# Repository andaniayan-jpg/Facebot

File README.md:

## Project Description

This is my small-scale AI smart assistant that I built completely from scratch using the ESP32-S3. I didn’t want to just make a simple breadboard project, so I designed a full custom PCB for it to make it look and feel like a proper product.

The device has a high-quality microphone with an amplifier so it can clearly pick up voice commands, and it also has a speaker so it can respond back properly. I added a TFT display to show smooth animations and expressions, so it doesn’t feel like a boring machine but more like a small gadget with some personality.

Everything is fitted inside a 3D-printed enclosure that I designed myself. I made sure the PCB, screen, mic, and speaker all fit properly and the finishing looks clean. This project combines hardware design, PCB making, wireless connectivity, and AI features into one compact device.

It’s basically my attempt at building a proper end-to-end AI gadget instead of just making a small demo.

## How to Use

1. Power the device using a USB cable.
2. Once it turns on, the TFT display will show an animation indicating that the assistant is ready.
3. Speak clearly near the microphone to give a voice command.
4. The assistant processes your request over Wi-Fi and responds back through the speaker.
5. The screen shows visual feedback while it is listening and responding.

Make sure the device is connected to Wi-Fi before using it for AI-based responses.

## Why I Made This Project

I made this project because I didn’t want to just keep learning things in theory. I wanted to actually build something real that combines electronics, coding, and AI in one proper device. Instead of copying some ready-made tutorial, I challenged myself to design everything — the PCB, the enclosure, and the full system integration.

I was also curious about how voice assistants actually work behind the scenes. We use them every day, but building one from scratch made me understand the hardware side, firmware side, and how wireless communication connects everything together.

This project was mainly about pushing myself to go beyond simple prototypes and create something that feels like an actual product.

## A full BOM.csv file is available in the repository further called as "BOM.csv"\

## Bill of Materials (BOM)

Full detailed BOM file: [BOM.csv](BOM.csv)

| Reference | Qty | Value / Part | Description | Purchase Link |
|------------|-----|--------------|--------------|---------------|
| C1, C4 | 2 | 10µF | Capacitor | https://in.element14.com/yageo/cc0805kkx7r7bb106/cap-10uf-16v-mlcc-0805/dp/3873445  |
| C2, C3 | 2 | 0.1µF | Capacitor | https://in.element14.com/multicomp-pro/mc0805b104k160ct/cap-0-1-f-16v-10-x7r-0805/dp/1759143  |
| J1 | 1 | USB_C_Receptacle_USB2.0_14P | USB Type-C Connector | https://in.element14.com/gct-global-connector-technology/usb4085-gf-a/usb-conn-2-0-type-c-r-a-rcpt-16pos/dp/2924867 |
| LS1 | 1 | Speaker | Speaker | https://in.element14.com/pui-audio/as04004pr-r/speaker-100hz-20khz-4ohm-86dba/dp/4412328  |
| MK1 | 1 | Microphone | Microphone | https://in.element14.com/multicomp-pro/abm-713-rc/electret-microphone-omni-pcb-pins/dp/2066499  |
| R1, R2 | 2 | Resistor | Resistor | https://in.element14.com/vishay/crcw060313k0fkea/res-13k-1-0-1w-0603-thick-film/dp/1652839 |
| SW1, SW2 | 3 | SW_Push | Push Button | https://in.element14.com/c-k-components/pts636-sm50-lfs/tactile-switch-0-05a-12vdc-180gf/dp/3780607  |
| U1 | 1 | ESP32-S3-WROOM-1 | Microcontroller Module | https://in.element14.com/dfrobot/dfr0975/dev-board-xtensa-lx7-wi-fi-bluetooth/dp/4733231 |
| U2 | 1 | EA_eDIPTFT32-A | TFT Display | https://robu.in/product/smartelex-3-2-tft-display-240x320/  |
| U3 | 1 | MAX9814 | Microphone Amplifier | https://in.element14.com/analog-devices/max9814etd-t/audio-amplifier-2-7v-to-5-5-tdfn/dp/2519088RL |
| U4 | 1 | MAX98357A | Audio Amplifier | https://in.element14.com/analog-devices/max98357aete-t/audio-power-amp-d-40-to-85deg/dp/2949165RL |
| U5 | 1 | AMS1117-3.3 | 3.3V Voltage Regulator | https://robu.in/product/ams1117-3-3v-1a-sot-223-voltage-regulator-ic-pack-of-5-ics/?gad_source=1&gad_campaignid=17427802703&gbraid=0AAAAADvLFWf1oom3zs2LMsp4jrXyl_zPl&gclid=EAIaIQobChMIlfeNufTqkgMVKpmmAx3wOBgwEAQYASABEgLSTPD_BwE |

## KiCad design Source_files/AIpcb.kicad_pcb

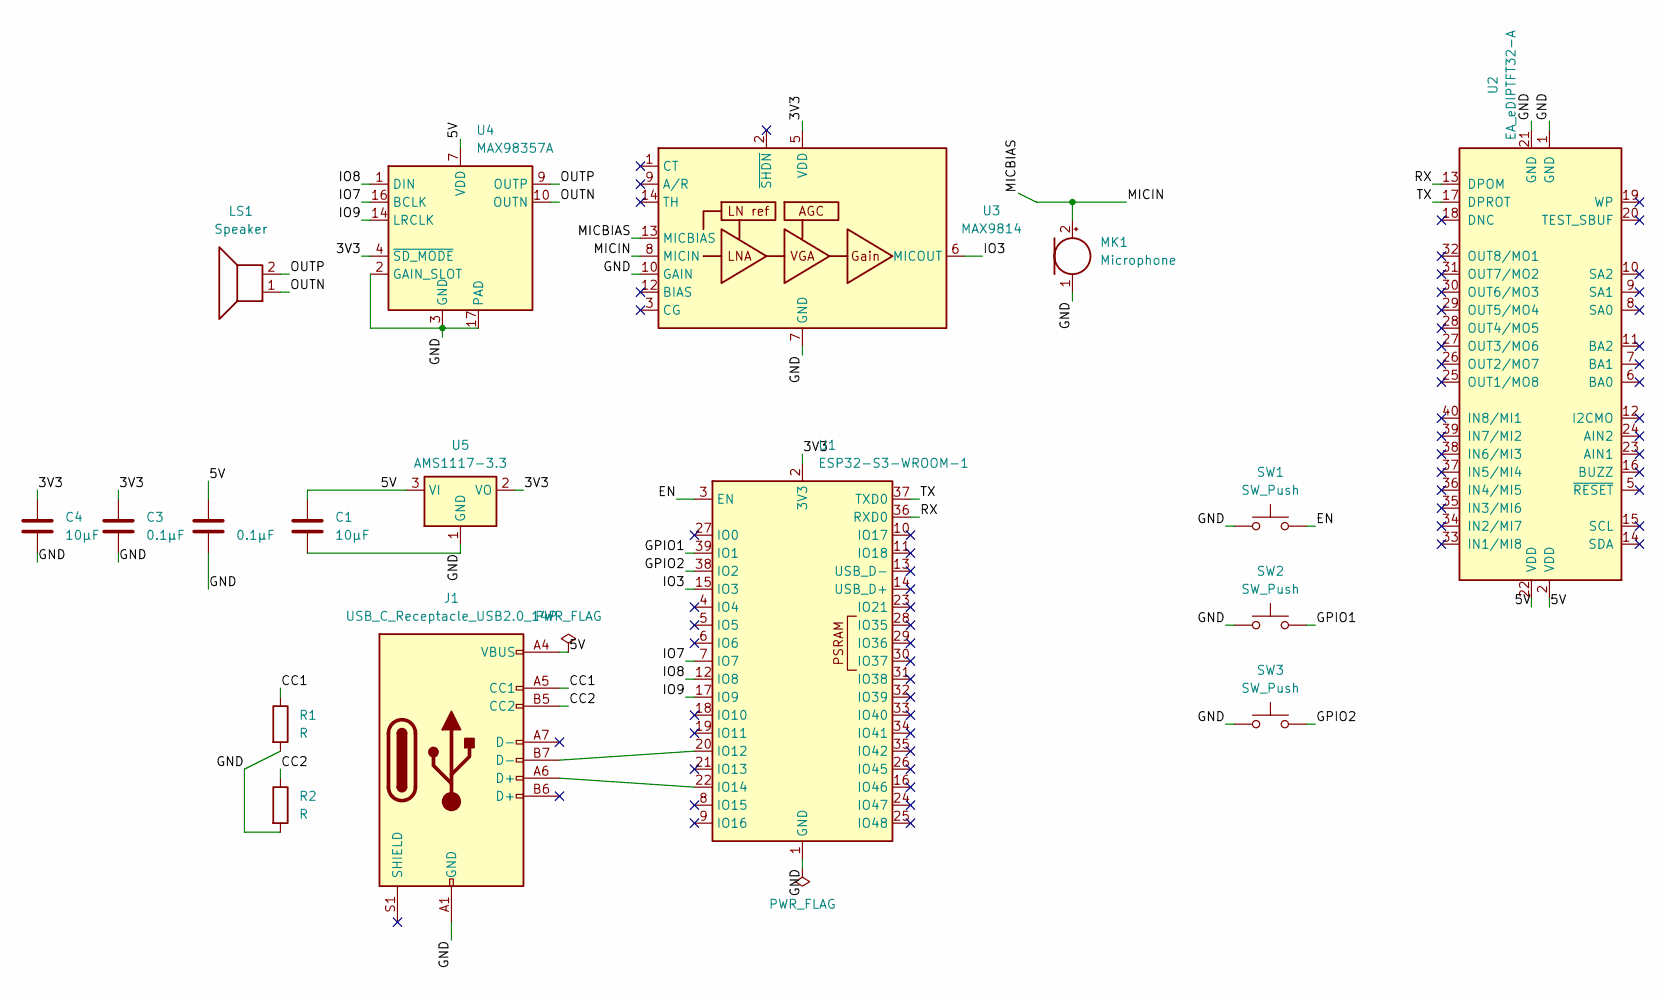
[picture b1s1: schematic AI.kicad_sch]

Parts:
C1, C4: 10µF; C_0805_2012Metric
C2, C3: 0.1µF; C_0603_1608Metric
J1: USB_C_Receptacle_USB2.0_14P; USB_C_Receptacle_GCT_USB4105-xx-A_16P_TopMnt_Horizontal
LS1: Speaker; PinHeader_1x02_P2.54mm_Horizontal
MK1: Microphone; PinHeader_1x02_P2.54mm_Horizontal
R1, R2: R; R_0603_1608Metric
SW1, SW2, SW3: SW_Push; SW_Tactile_SPST_NO_Straight_CK_PTS636Sx25SMTRLFS
U1: ESP32-S3-WROOM-1
U2: EA_eDIPTFT32-A; EA_eDIPTFT32-XXX
U3: MAX9814; DFN-14-1EP_3x3mm_P0.4mm_EP1.78x2.35mm
U4: MAX98357A; TQFN-16-1EP_3x3mm_P0.5mm_EP1.23x1.23mm
U5: AMS1117-3.3; SOT-223-3_TabPin2

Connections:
/3V3: C3.1, C4.1, U1.2 (3V3), U3.5 (VDD), U4.4 (~SD_MODE), U5.2 (VO)
/5V: C1.1, C2.1, J1.A4 (VBUS), J1.A9 (VBUS), J1.B4 (VBUS), J1.B9 (VBUS), U2.2 (VDD), U2.22 (VDD), U4.7 (VDD), U4.8 (VDD), U5.3 (VI)
/CC1: J1.A5 (CC1), R1.1
/CC2: J1.B5 (CC2), R2.1
/EN: SW1.2, U1.3 (EN)
/GND: C1.2, C2.2, C3.2, C4.2, J1.A1 (GND), J1.A12 (GND), J1.B1 (GND), J1.B12 (GND), MK1.1 (-), R1.2, R2.2, SW1.1, SW2.1, SW3.1, U1.1 (GND), U1.40 (GND), U1.41 (GND), U2.1 (GND), U2.21 (GND), U3.4 (GND), U3.7 (GND), U3.10 (GAIN), U3.11 (GND), U3.15 (GND), U4.2 (GAIN_SLOT), U4.3 (GND), U4.11 (GND), U4.15 (GND), U4.17 (PAD), U5.1 (GND)
/GPIO1: SW2.2, U1.39 (IO1)
/GPIO2: SW3.2, U1.38 (IO2)
/IO3: U1.15 (IO3), U3.6 (MICOUT)
/IO7: U1.7 (IO7), U4.16 (BCLK)
/IO8: U1.12 (IO8), U4.1 (DIN)
/IO9: U1.17 (IO9), U4.14 (LRCLK)
/MICBIAS: MK1.2 (+), U3.8 (MICIN), U3.13 (MICBIAS)
/OUTN: LS1.1, U4.10 (OUTN)
/OUTP: LS1.2, U4.9 (OUTP)
/RX: U1.36 (RXD0), U2.13 (DPOM)
/TX: U1.37 (TXD0), U2.17 (DPROT)
unnamed: J1.B7 (D-), U1.20 (IO12)
unnamed: J1.A6 (D+), U1.22 (IO14)

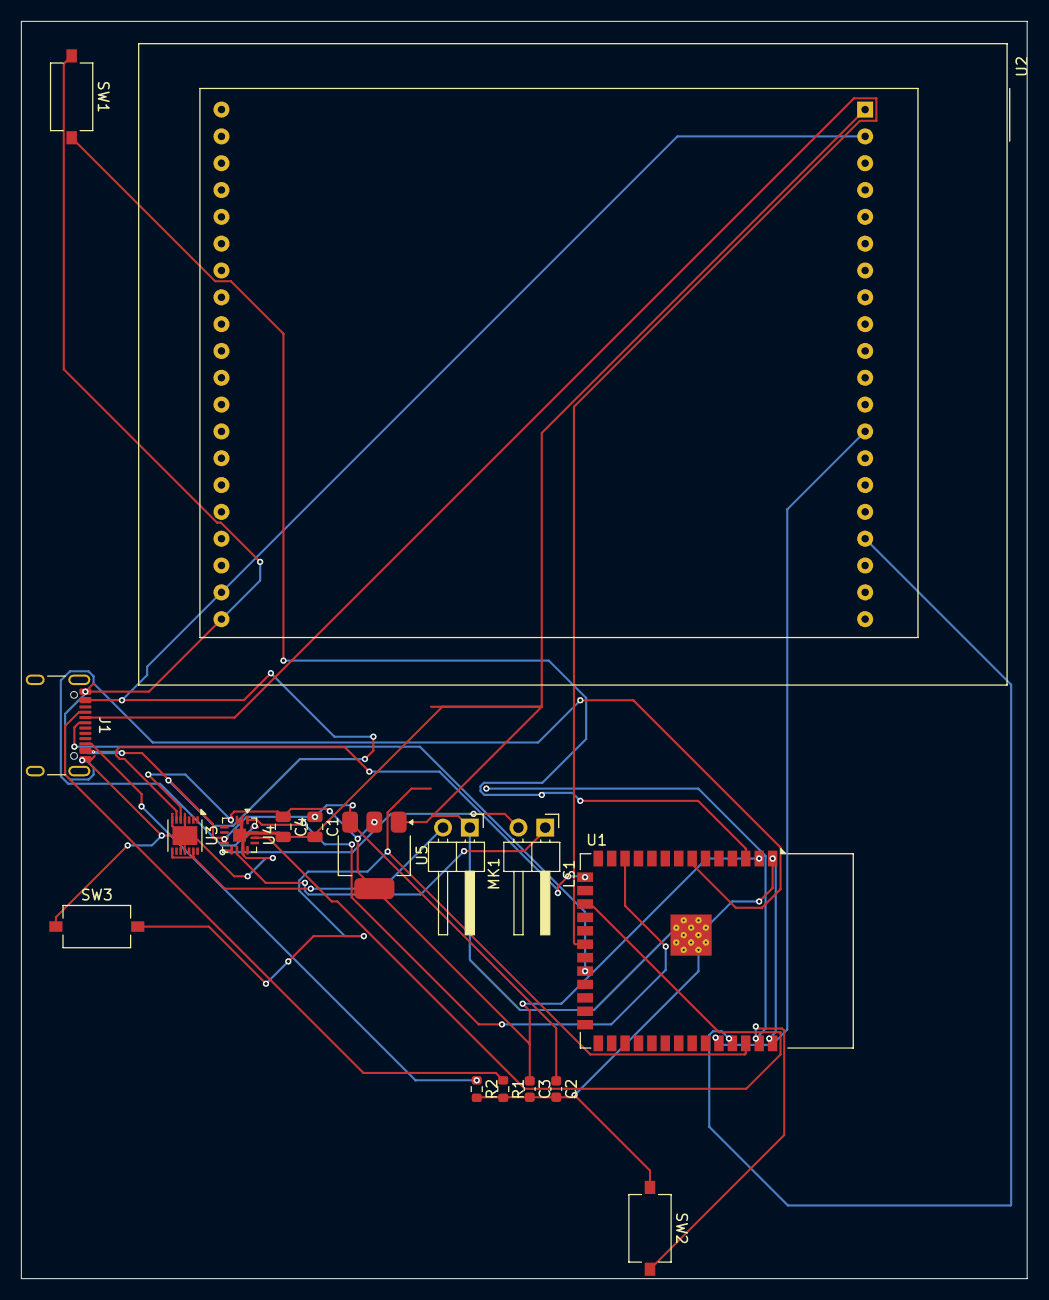
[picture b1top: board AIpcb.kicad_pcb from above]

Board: 2 copper layers, 95.3 x 119.1 mm, 17 parts (0 on the bottom side), 19 nets.

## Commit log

2026-02-24 Add README with project details and usage instructions
    Added project description, usage instructions, and motivation for creating the AI smart assistant. Included images and a note about the BOM file.
2026-02-24 Add initial KiCad project configuration
2026-02-24 Create op
2026-02-26 Create firmware
